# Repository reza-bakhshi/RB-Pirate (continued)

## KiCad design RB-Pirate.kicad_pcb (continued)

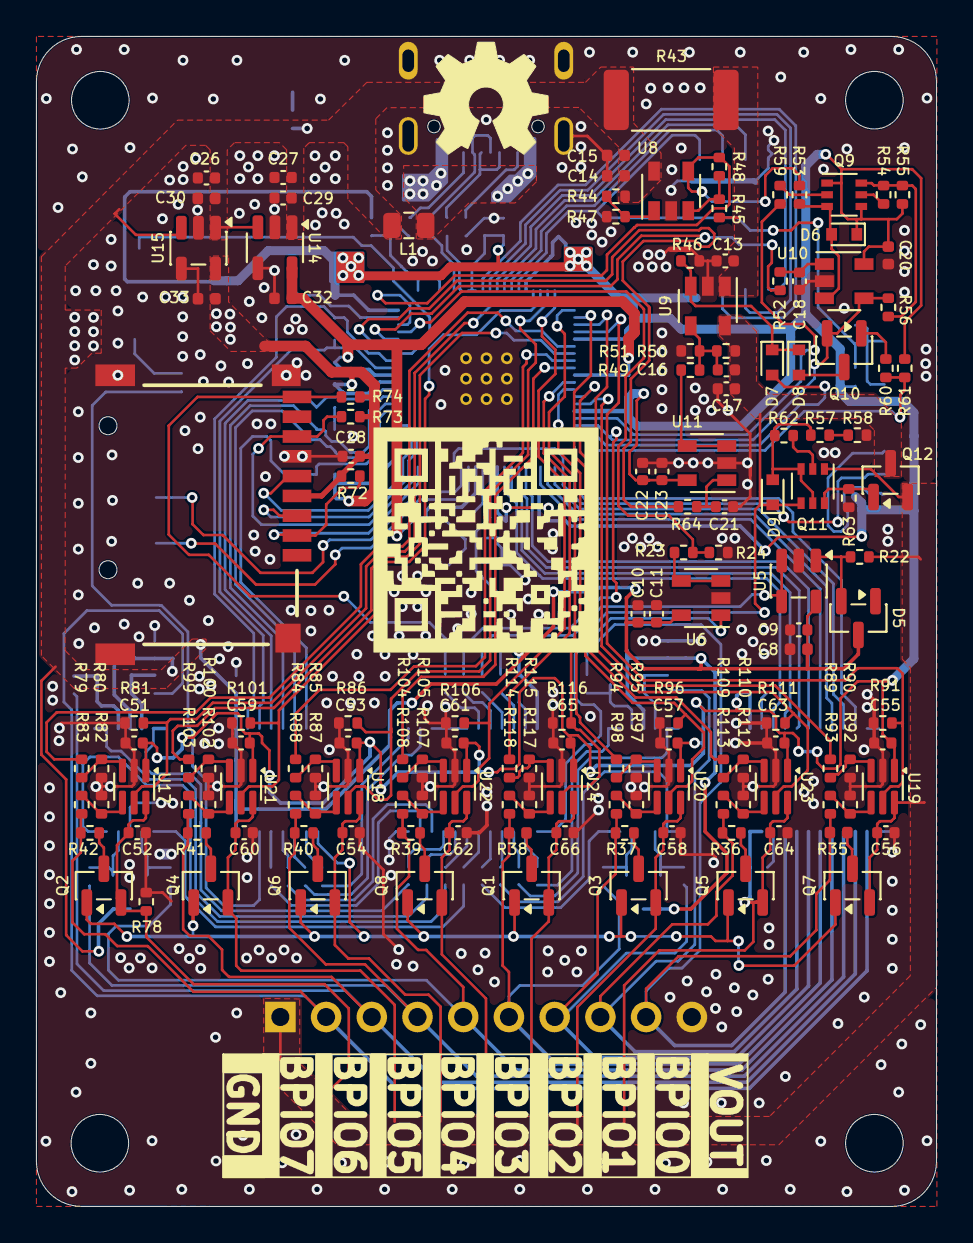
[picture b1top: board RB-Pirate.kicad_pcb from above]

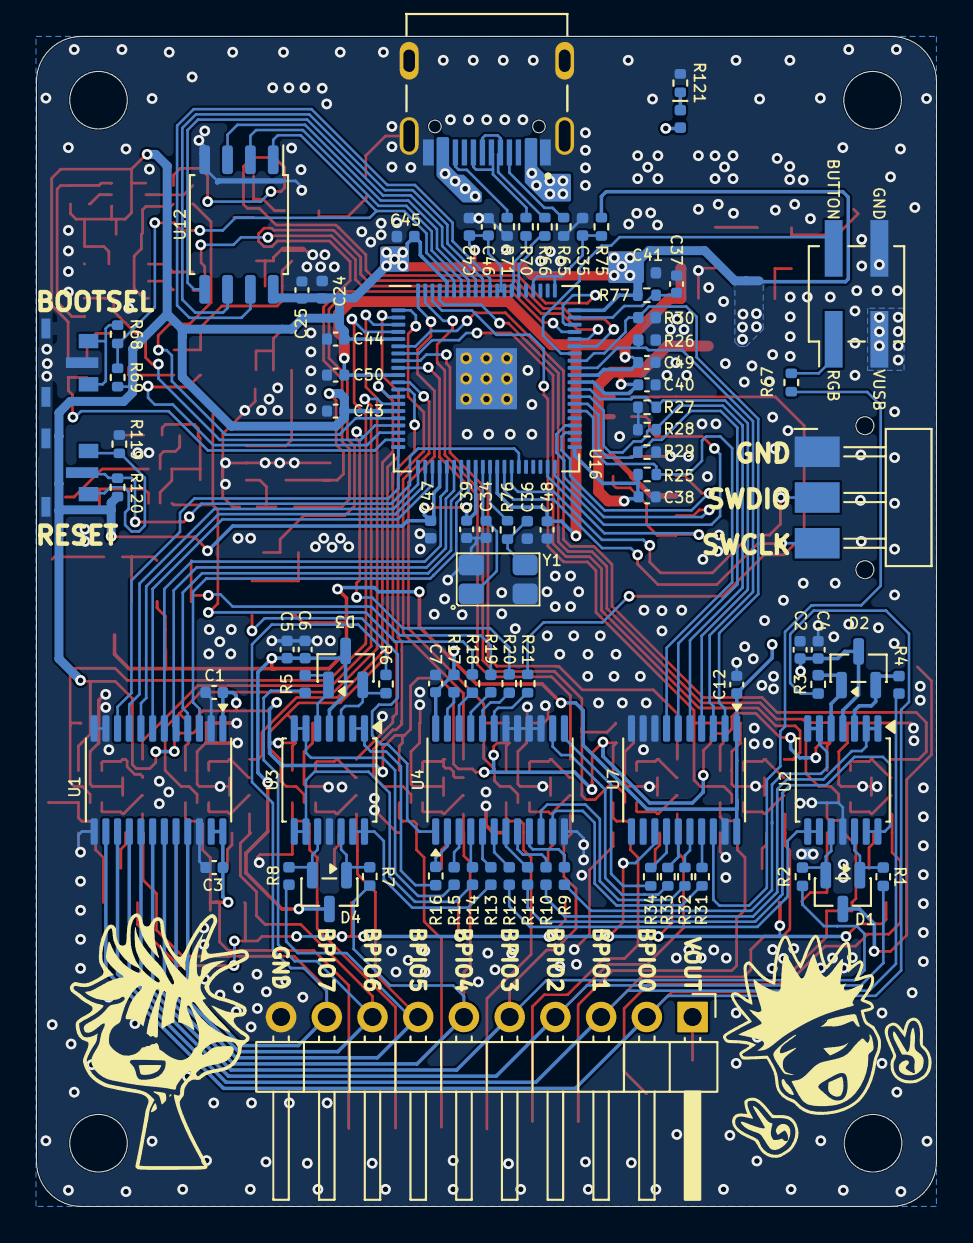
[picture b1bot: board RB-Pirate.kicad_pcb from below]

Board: 2 copper layers, 50.0 x 65.0 mm, 244 parts (94 on the bottom side), 168 nets.

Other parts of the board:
Ref**: Val**; OSHW_Logo_7mm
